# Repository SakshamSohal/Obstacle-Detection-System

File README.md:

Modular Ultrasonic Obstacle Detection System

A basic and low-cost system using Arduino Nano and HC-SR04 to detect obstacles and indicate distance zones via LEDs. Designed with modularity in mind for future integration into UAVs and robotics platforms.

 Project Overview

- **Distance sensing** with HC-SR04
- **Visual alerts** using Red, Yellow, and Green LEDs
- **Custom PCB** designed in KiCAD 9 
- **Arduino-based firmware** for control and detection logic

---
 Components & Pin Mapping

| Component        | Arduino Nano Pin |
|-----------------|------------------|
| HC-SR04 Trig     | D9               |
| HC-SR04 Echo     | D7               |
| Green LED        | D2               |
| Yellow LED       | D3               |
| Red LED          | D4              |

Power and ground connections are shared among all components.

---

 Arduino Code Summary

The Arduino sketch reads distance from the sensor and lights the appropriate LED:
- **Green**: Safe (>100 cm)
- **Yellow**: Caution (50–100 cm)
- **Red**: Danger (<50 cm)

  Summary: A modular ultrasonic obstacle detection system with Arduino Nano as the Microcontroller unit. Developed an Arduino code for this detection system as well as designed a custom made PCB ready for fabrication.

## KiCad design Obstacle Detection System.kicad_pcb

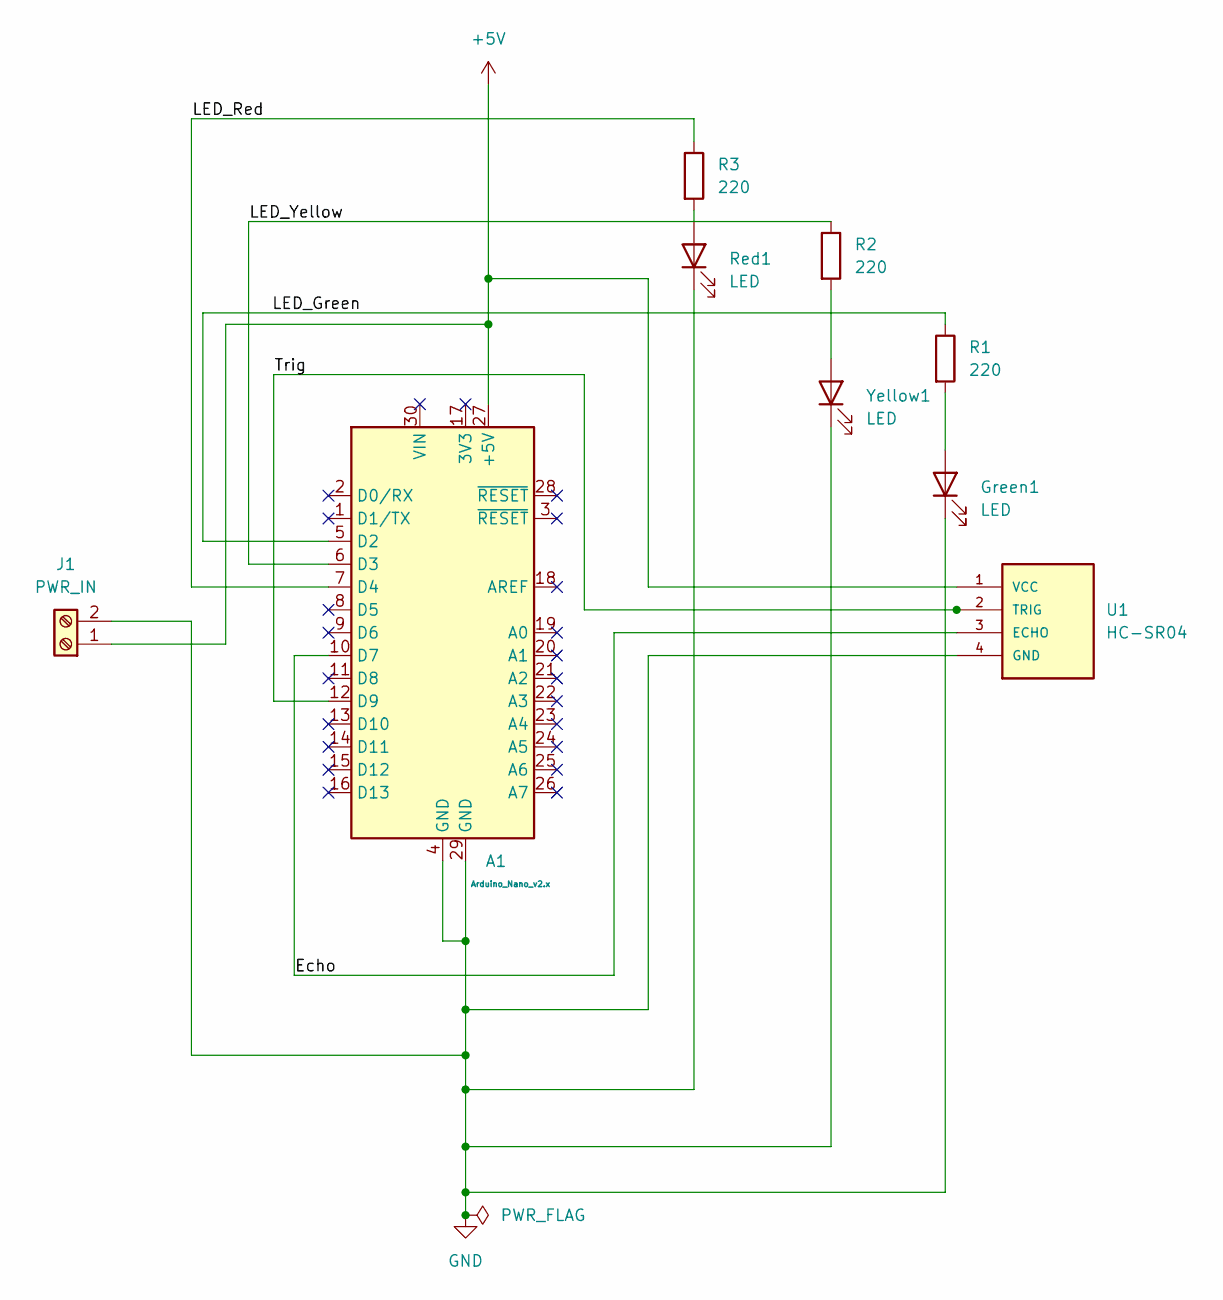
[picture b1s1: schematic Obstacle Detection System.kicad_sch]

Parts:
A1: Arduino_Nano_v2.x; Arduino_Nano
Green1: LED; LED_D5.0mm
J1: PWR_IN; PinHeader_1x02_P2.54mm_Vertical
R1, R2, R3: 220; R_Axial_DIN0207_L6.3mm_D2.5mm_P7.62mm_Horizontal
Red1: LED; LED_D5.0mm
U1: HC-SR04; XCVR_HC-SR04
Yellow1: LED; LED_D5.0mm

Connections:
+5V: A1.27 (+5V), J1.1 (5V), U1.1 (VCC)
/Echo: A1.10 (D7), U1.3 (ECHO)
/LED_Green: A1.5 (D2), R1.1
/LED_Red: A1.7 (D4), R3.1
/LED_Yellow: A1.6 (D3), R2.1
/Trig: A1.12 (D9), U1.2 (TRIG)
GND: A1.4 (GND), A1.29 (GND), Green1.1 (K), J1.2 (GND), Red1.1 (K), U1.4 (GND), Yellow1.1 (K)
unnamed: Green1.2 (A), R1.2
unnamed: R3.2, Red1.2 (A)
unnamed: R2.2, Yellow1.2 (A)

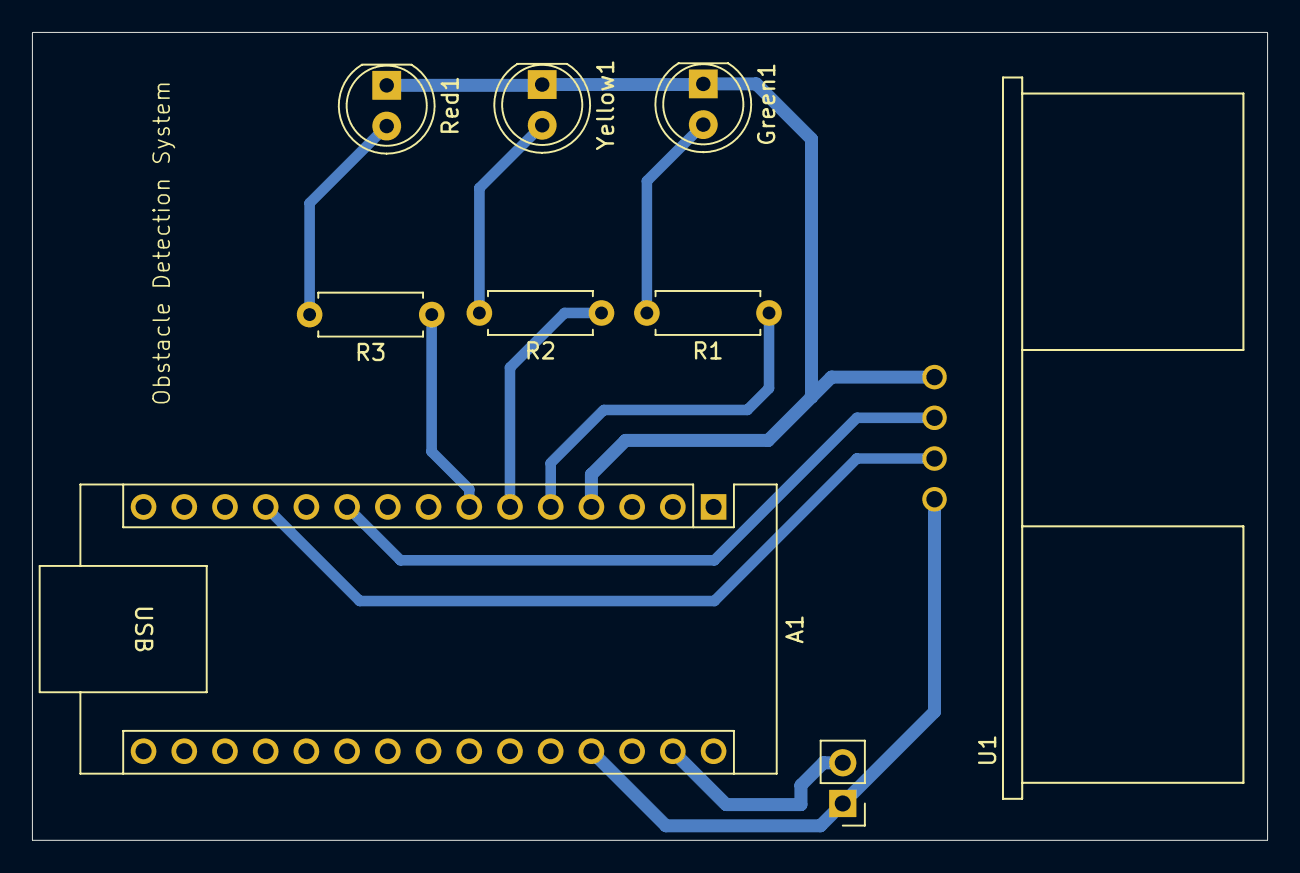
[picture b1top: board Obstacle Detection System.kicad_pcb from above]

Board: 2 copper layers, 77.0 x 50.4 mm, 9 parts (0 on the bottom side), 10 nets.
